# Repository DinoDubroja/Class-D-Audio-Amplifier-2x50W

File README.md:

# Class-D-Audio-Amplifier-2x50W

High-quality stereo class D audio amplifier (2x50W). The board is based on Texas Instruments TPA3118D2 (Class D amplifier IC). Adding a heatsink to the IC is necessary to fully utilize this board's power capabilities. 

All parts I used are listed in BOM and part numbers for Mouser Electronics are provided. Values of filter capacitors can be changed to optimize t for subwoofer operation. If you want to do this please refer to the datasheet of the IC and application circuit provided.

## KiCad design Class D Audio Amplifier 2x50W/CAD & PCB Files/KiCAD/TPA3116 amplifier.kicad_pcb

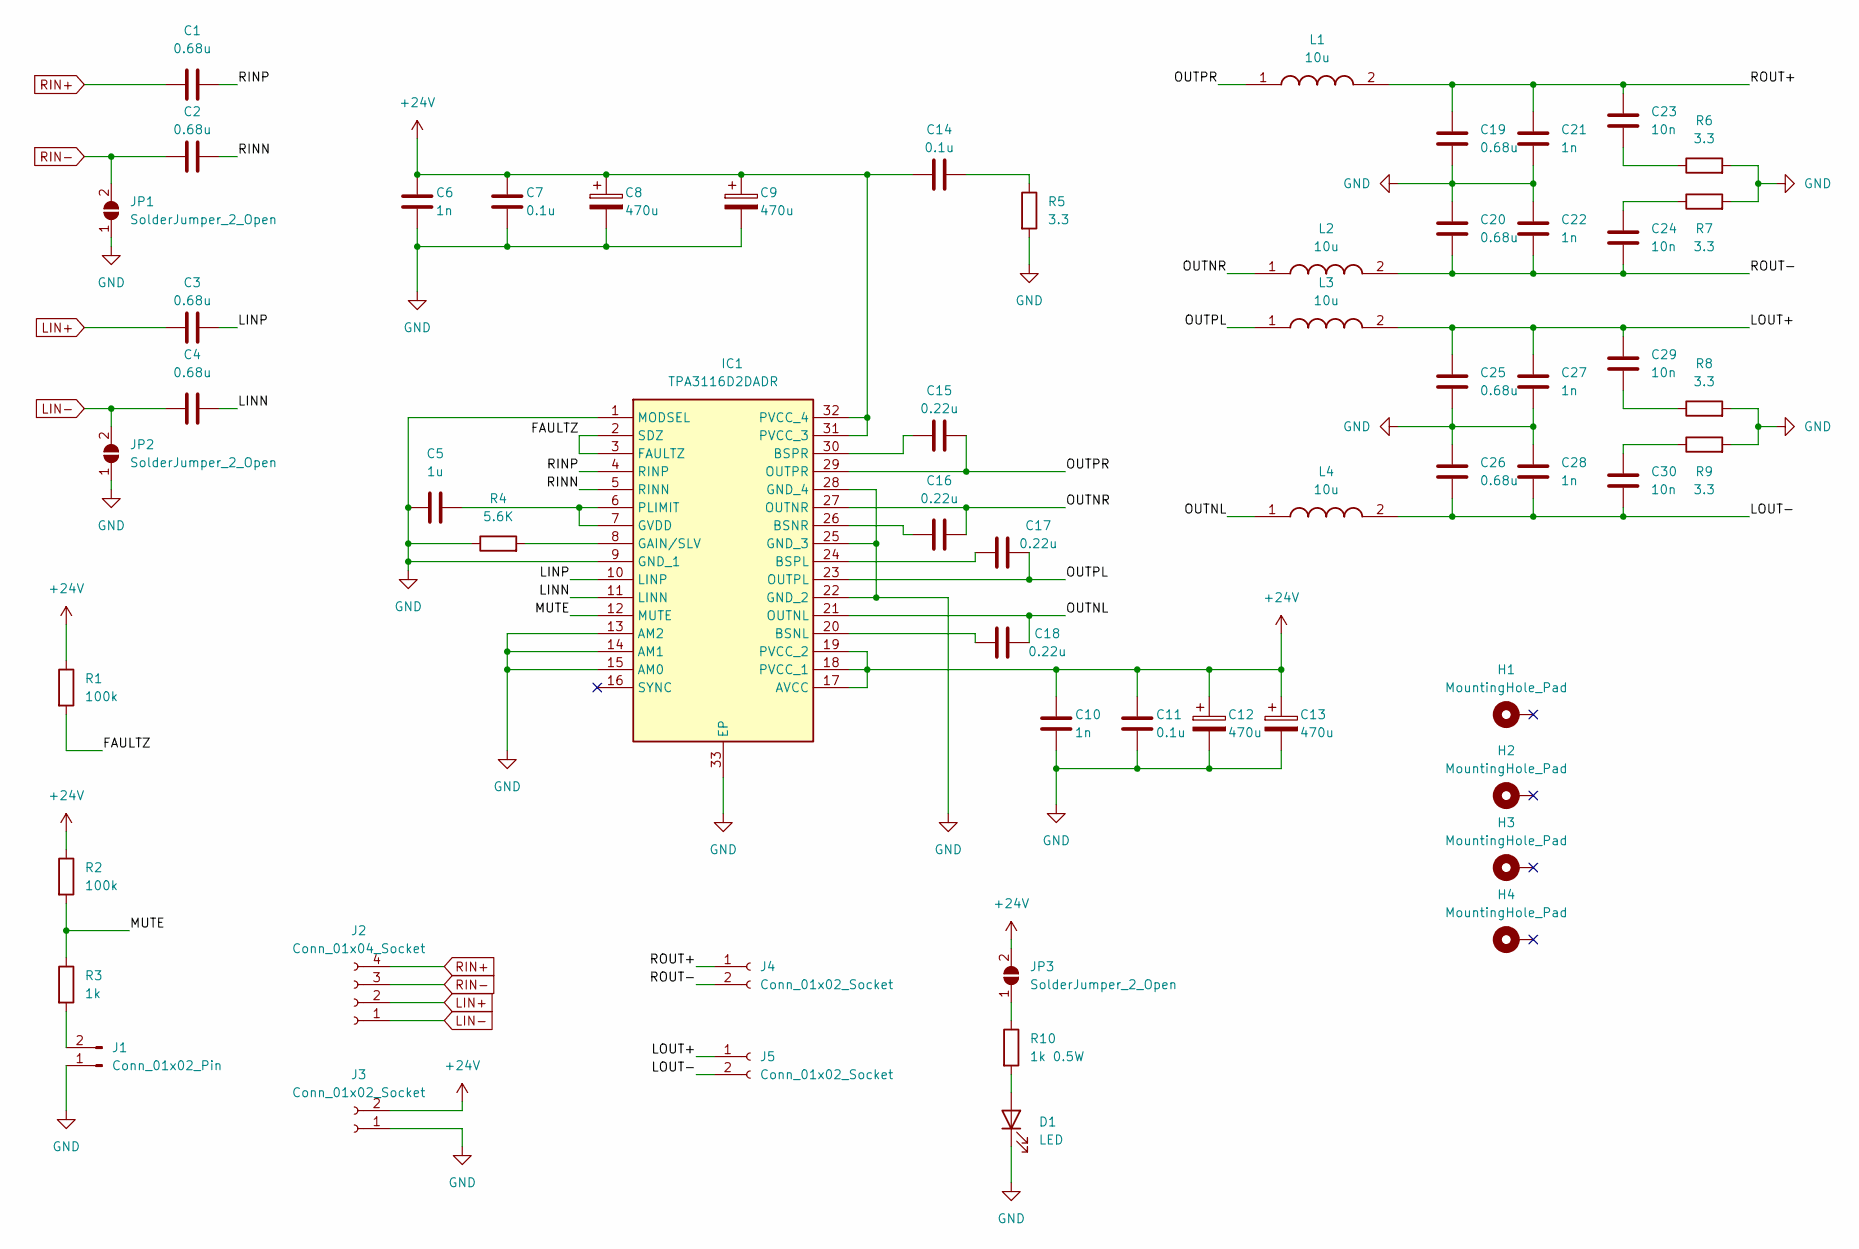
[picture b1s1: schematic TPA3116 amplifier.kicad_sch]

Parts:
C1, C2, C3, C4, C19, C20, C25, C26: 0.68u; C_0805_2012Metric_Pad1.18x1.45mm_HandSolder
C5: 1u; C_0805_2012Metric_Pad1.18x1.45mm_HandSolder
C6, C10, C21, C22, C27, C28: 1n; C_0805_2012Metric_Pad1.18x1.45mm_HandSolder
C7, C11, C14: 0.1u; C_0805_2012Metric_Pad1.18x1.45mm_HandSolder
C8, C9, C12, C13: 470u; CP_Radial_D16.0mm_P7.50mm
C15, C16, C17, C18: 0.22u; C_0805_2012Metric_Pad1.18x1.45mm_HandSolder
C23, C24, C29, C30: 10n; C_0805_2012Metric_Pad1.18x1.45mm_HandSolder
D1: LED; LED_1206_3216Metric
H1, H2, H3, H4: MountingHole_Pad; MountingHole_3.2mm_M3_Pad_Via
IC1: TPA3116D2DADR; SOP65P810X120-33N; Mouser Part Number 595-TPA3116D2DADR
J1: Conn_01x02_Pin; PinSocket_1x02_P2.54mm_Vertical
J2: Conn_01x04_Socket; TB00150004BE
J3, J4, J5: Conn_01x02_Socket; TB00150002BE
JP1, JP2, JP3: SolderJumper_2_Open; SolderJumper-2_P1.3mm_Open_TrianglePad1.0x1.5mm
L1, L2, L3, L4: 10u; 104CDMCCDS100MC; Mouser Part Number 851-104CDMCCDS-100MC
R1, R2: 100k; R_0805_2012Metric_Pad1.20x1.40mm_HandSolder
R3: 1k; R_0805_2012Metric_Pad1.20x1.40mm_HandSolder
R4: 5.6K; R_0805_2012Metric_Pad1.20x1.40mm_HandSolder
R5, R6, R7, R8, R9: 3.3; R_0805_2012Metric_Pad1.20x1.40mm_HandSolder
R10: 1k 0.5W; R_1206_3216Metric_Pad1.30x1.75mm_HandSolder

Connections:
+24V: C6.2, C7.2, C8.1, C9.1, C10.2, C11.2, C12.1, C13.1, C14.1, IC1.17 (AVCC), IC1.18 (PVCC_1), IC1.19 (PVCC_2), IC1.31 (PVCC_3), IC1.32 (PVCC_4), J3.2, JP3.2 (B), R1.1, R2.1
/FAULTZ: IC1.2 (SDZ), IC1.3 (FAULTZ), R1.2
/LINN: C4.2, IC1.11 (LINN)
/LINP: C3.2, IC1.10 (LINP)
/LOUT+: C25.1, C27.1, C29.1, J5.1, L3.2
/LOUT-: C26.2, C28.2, C30.2, J5.2, L4.2
/MUTE: IC1.12 (MUTE), R2.2, R3.1
/OUTNL: C18.2, IC1.21 (OUTNL), L4.1
/OUTNR: C16.2, IC1.27 (OUTNR), L2.1
/OUTPL: C17.2, IC1.23 (OUTPL), L3.1
/OUTPR: C15.2, IC1.29 (OUTPR), L1.1
/RINN: C2.2, IC1.5 (RINN)
/RINP: C1.2, IC1.4 (RINP)
/ROUT+: C19.1, C21.1, C23.1, J4.1, L1.2
/ROUT-: C20.2, C22.2, C24.2, J4.2, L2.2
GND: C5.2, C6.1, C7.1, C8.2, C9.2, C10.1, C11.1, C12.2, C13.2, C19.2, C20.1, C21.2, C22.1, C25.2, C26.1, C27.2, C28.1, D1.1 (K), IC1.1 (MODSEL), IC1.9 (GND_1), IC1.13 (AM2), IC1.14 (AM1), IC1.15 (AM0), IC1.22 (GND_2), IC1.25 (GND_3), IC1.28 (GND_4), IC1.33 (EP), J1.1, J3.1, JP1.1 (A), JP2.1 (A), R4.1, R5.2, R6.2, R7.2, R8.2, R9.2
LIN+: C3.1, J2.2
LIN-: C4.1, J2.1, JP2.2 (B)
unnamed: C14.2, R5.1
unnamed: C23.2, R6.1
unnamed: C24.1, R7.1
unnamed: C29.2, R8.1
unnamed: C30.1, R9.1
unnamed: D1.2 (A), R10.2
unnamed: C18.1, IC1.20 (BSNL)
unnamed: C16.1, IC1.26 (BSNR)
unnamed: C17.1, IC1.24 (BSPL)
unnamed: C15.1, IC1.30 (BSPR)
unnamed: IC1.8 (GAIN/SLV), R4.2
unnamed: C5.1, IC1.6 (PLIMIT), IC1.7 (GVDD)
unnamed: J1.2, R3.2
unnamed: JP3.1 (A), R10.1
RIN+: C1.1, J2.4
RIN-: C2.1, J2.3, JP1.2 (B)

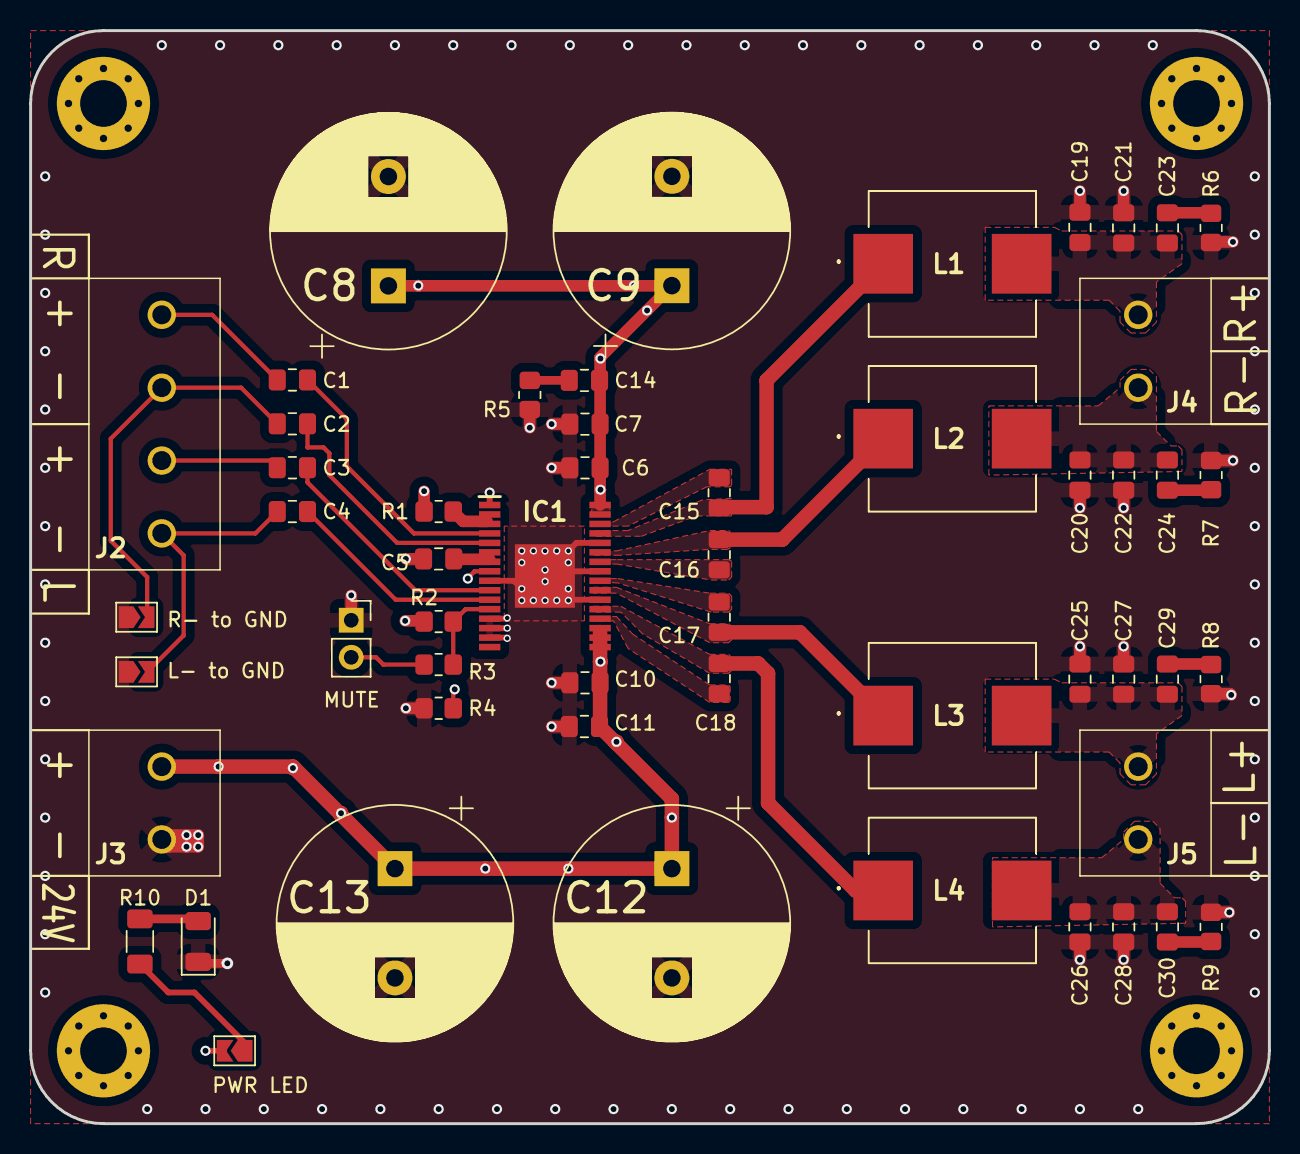
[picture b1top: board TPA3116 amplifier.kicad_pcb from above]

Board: 4 copper layers, 85.0 x 75.0 mm, 58 parts (0 on the bottom side), 34 nets.
